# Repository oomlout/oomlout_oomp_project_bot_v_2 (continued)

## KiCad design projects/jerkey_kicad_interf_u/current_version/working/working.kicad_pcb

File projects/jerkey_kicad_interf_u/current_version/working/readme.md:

# kicad
 
## summary 
* id: jerkey_kicad_interf_u
* user: jerkey
* name: kicad
* board: interf_u
* repo: https://github.com/jerkey/kicad
* src_file_repo_kicad_pcb: demos/interf_u/interf_u.kicad_pcb
* src_file_repo_kicad_pcb_link: https://github.com/jerkey/kicad/tree/master/demos/interf_u/interf_u.kicad_pcb

* src_file_repo_sch: demos/interf_u/interf_u.sch
* src_file_repo_sch_link: https://github.com/jerkey/kicad/tree/master/demos/interf_u/interf_u.sch
* full details link: https://github.com/oomlout/oomlout_oomp_project_bot_v_2/tree/main/projects/jerkey_kicad_interf_u/current_version/working

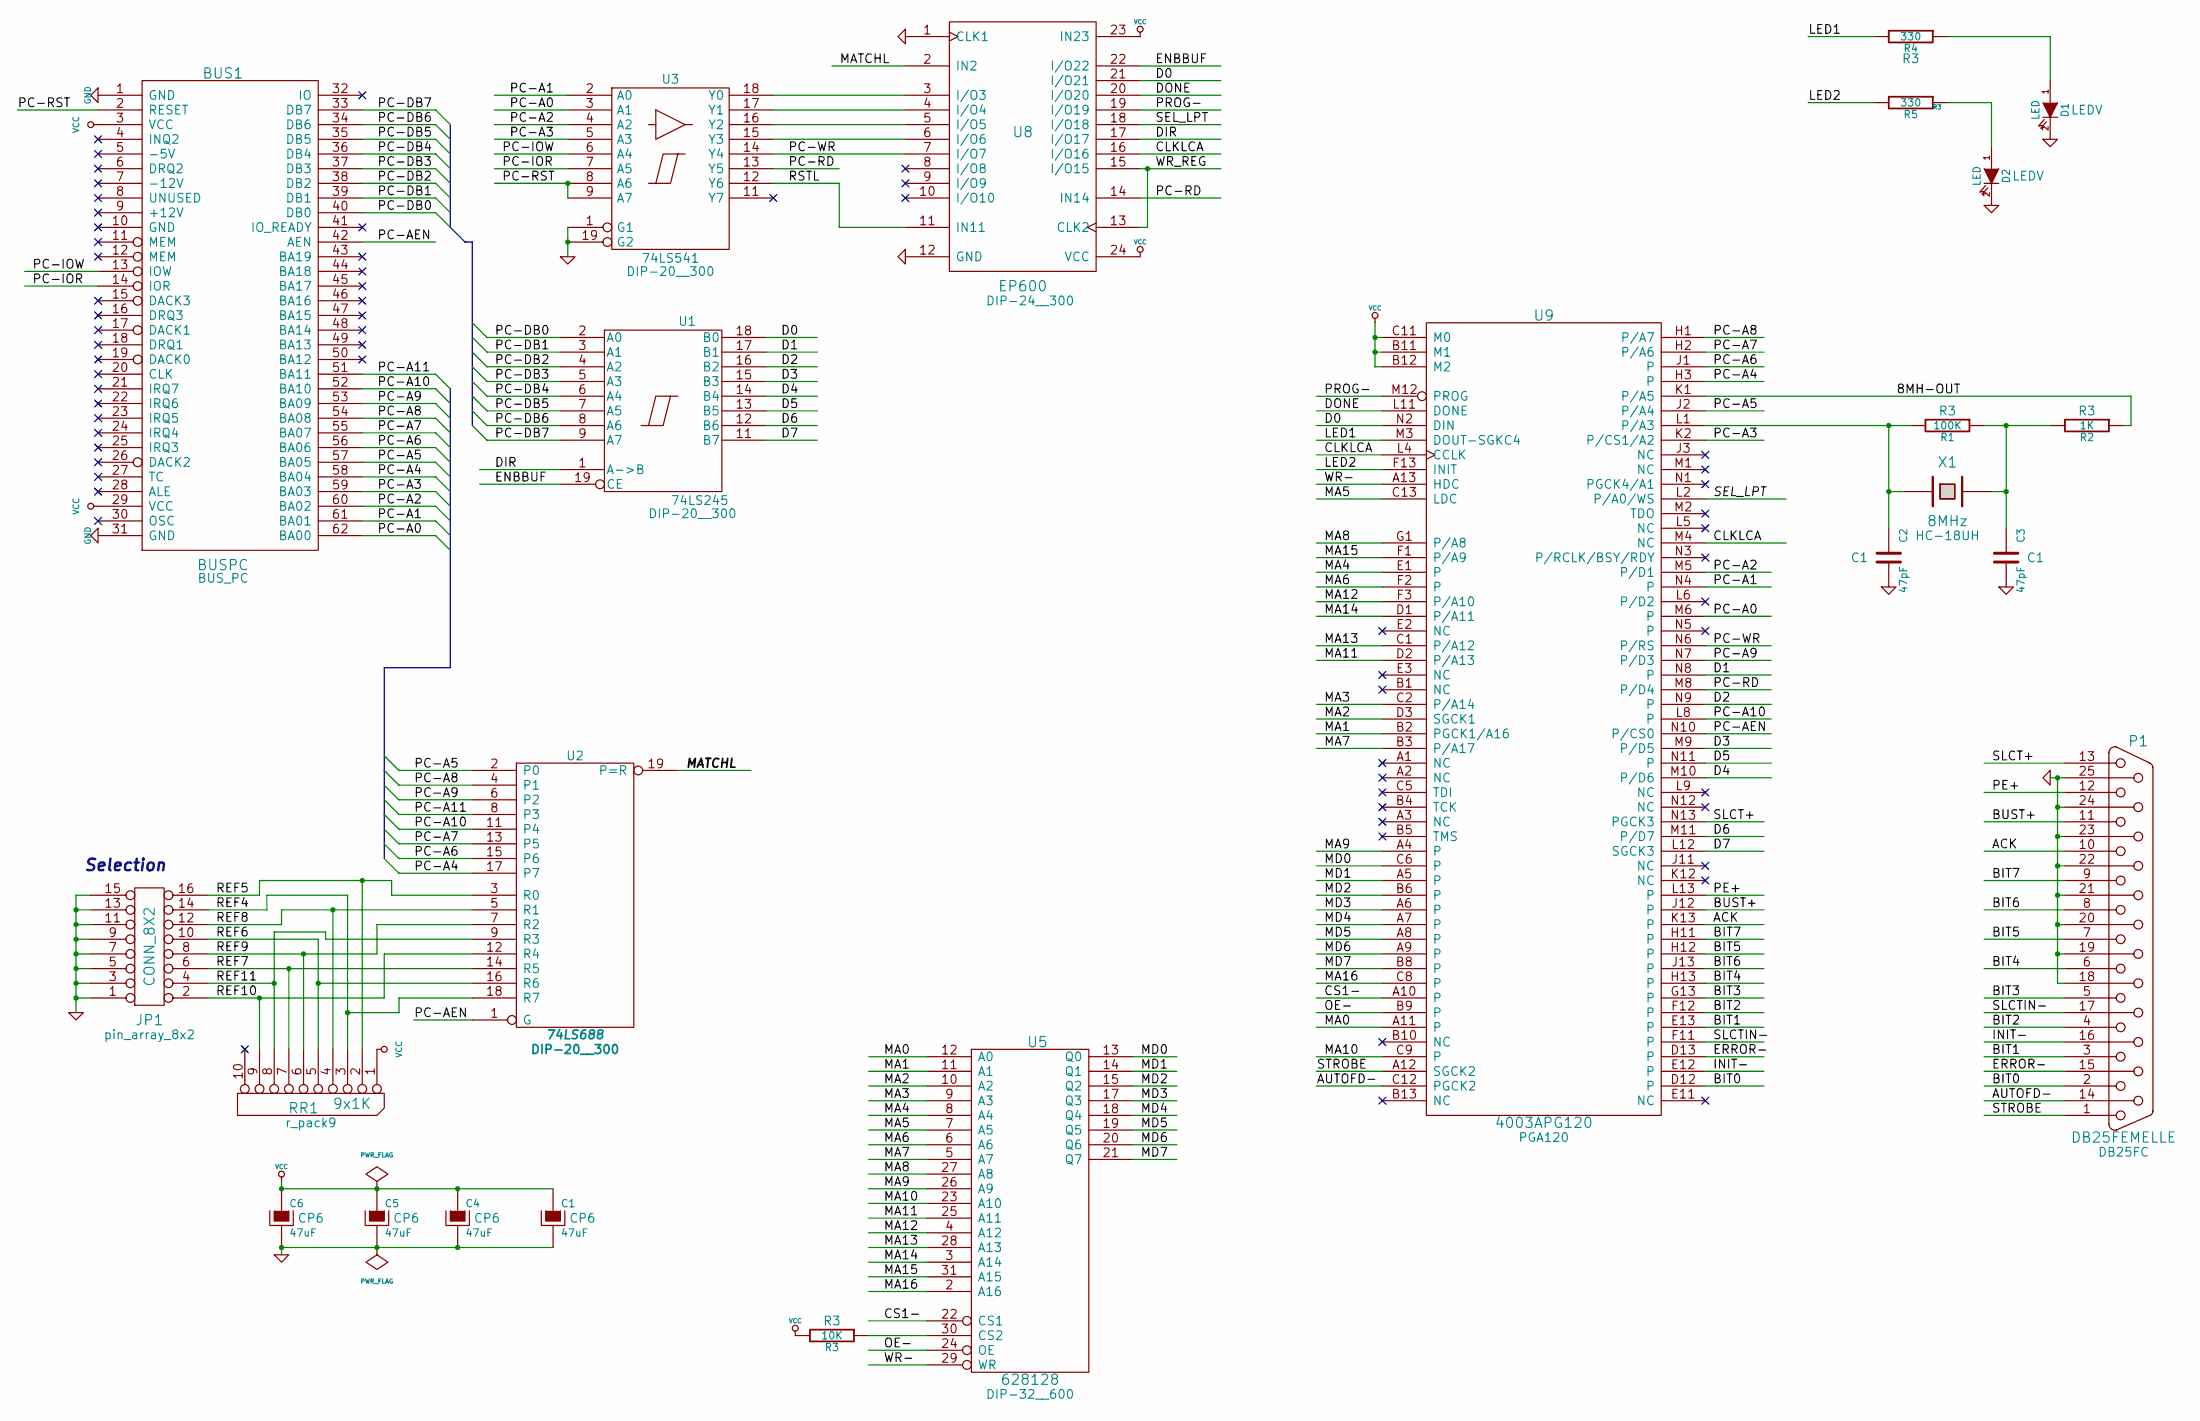
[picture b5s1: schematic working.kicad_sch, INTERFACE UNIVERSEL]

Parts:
BUS1: BUSPC; BUS_PC
C1, C4, C5, C6: 47uF; CP6
C2, C3: 47pF; C1
D1, D2: LED; LEDV
JP1: CONN_8X2; pin_array_8x2
P1: DB25FEMELLE; DB25FC
R1: 100K; R3
R2: 1K; R3
R3: 10K; R3
R4, R5: 330; R3
RR1: 9x1K; r_pack9
U1: 74LS245; DIP-20__300
U2: 74LS688; DIP-20__300
U3: 74LS541; DIP-20__300
U5: 628128; DIP-32__600
U8: EP600; DIP-24__300
U9: 4003APG120; PGA120
X1: 8MHz; HC-18UH

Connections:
/8MH-OUT: R2.1, U9.K1 (P/A5)
/ACK: P1.10, U9.K13
/AUTOFD-: P1.14, U9.C12 (PGCK2)
/BIT0: P1.2, U9.D12
/BIT1: P1.3, U9.E13
/BIT2: P1.4, U9.F12
/BIT3: P1.5, U9.G13
/BIT4: P1.6, U9.H13
/BIT5: P1.7, U9.H12
/BIT6: P1.8, U9.J13
/BIT7: P1.9, U9.H11
/BUST+: P1.11, U9.J12
/CLKLCA: U8.16 (I/O16), U9.L4 (CCLK), U9.M4 (NC)
/CS1-: U5.22 (CS1), U9.A10
/D0: U1.18 (B0), U8.21 (I/O21), U9.N2 (DIN)
/D1: U1.17 (B1), U9.N8
/D2: U1.16 (B2), U9.N9
/D3: U1.15 (B3), U9.M9 (P/D5)
/D4: U1.14 (B4), U9.M10 (P/D6)
/D5: U1.13 (B5), U9.N11
/D6: U1.12 (B6), U9.M11 (P/D7)
/D7: U1.11 (B7), U9.L12 (SGCK3)
/DIR: U1.1 (A->B), U8.17 (I/O17)
/DONE: U8.20 (I/O20), U9.L11 (DONE)
/ENBBUF: U1.19 (CE), U8.22 (I/O22)
/ERROR-: P1.15, U9.D13
/INIT-: P1.16, U9.E12
/LED1: R4.2, U9.M3 (DOUT-SGKC4)
/LED2: R5.2, U9.F13 (INIT)
/MA0: U5.12 (A0), U9.A11
/MA1: U5.11 (A1), U9.B2 (PGCK1/A16)
/MA2: U5.10 (A2), U9.D3 (SGCK1)
/MA3: U5.9 (A3), U9.C2 (P/A14)
/MA4: U5.8 (A4), U9.E1
/MA5: U5.7 (A5), U9.C13 (LDC)
/MA6: U5.6 (A6), U9.F2
/MA7: U5.5 (A7), U9.B3 (P/A17)
/MA8: U5.27 (A8), U9.G1 (P/A8)
/MA9: U5.26 (A9), U9.A4
/MA10: U5.23 (A10), U9.C9
/MA11: U5.25 (A11), U9.D2 (P/A13)
/MA12: U5.4 (A12), U9.F3 (P/A10)
/MA13: U5.28 (A13), U9.C1 (P/A12)
/MA14: U5.3 (A14), U9.D1 (P/A11)
/MA15: U5.31 (A15), U9.F1 (P/A9)
/MA16: U5.2 (A16), U9.C8
/MATCHL: U2.19 (P=R), U8.2 (IN2)
/MD0: U5.13 (Q0), U9.C6
/MD1: U5.14 (Q1), U9.A5
/MD2: U5.15 (Q2), U9.B6
/MD3: U5.17 (Q3), U9.A6
/MD4: U5.18 (Q4), U9.A7
/MD5: U5.19 (Q5), U9.A8
/MD6: U5.20 (Q6), U9.A9
/MD7: U5.21 (Q7), U9.B8
/OE-: U5.24 (OE), U9.B9
/PC-A0: BUS1.62 (BA00), U3.3 (A1), U9.M6
/PC-A1: BUS1.61 (BA01), U3.2 (A0), U9.N4
/PC-A2: BUS1.60 (BA02), U3.4 (A2), U9.M5 (P/D1)
/PC-A3: BUS1.59 (BA03), U3.5 (A3), U9.K2 (P/CS1/A2)
/PC-A4: BUS1.58 (BA04), U2.17 (P7), U9.H3
/PC-A5: BUS1.57 (BA05), U2.2 (P0), U9.J2 (P/A4)
/PC-A6: BUS1.56 (BA06), U2.15 (P6), U9.J1
/PC-A7: BUS1.55 (BA07), U2.13 (P5), U9.H2 (P/A6)
/PC-A8: BUS1.54 (BA08), U2.4 (P1), U9.H1 (P/A7)
/PC-A9: BUS1.53 (BA09), U2.6 (P2), U9.N7 (P/D3)
/PC-A10: BUS1.52 (BA10), U2.11 (P4), U9.L8
/PC-A11: BUS1.51 (BA11), U2.8 (P3)
/PC-AEN: BUS1.42 (AEN), U2.1 (G), U9.N10 (P/CS0)
/PC-DB0: BUS1.40 (DB0), U1.2 (A0)
/PC-DB1: BUS1.39 (DB1), U1.3 (A1)
/PC-DB2: BUS1.38 (DB2), U1.4 (A2)
/PC-DB3: BUS1.37 (DB3), U1.5 (A3)
/PC-DB4: BUS1.36 (DB4), U1.6 (A4)
/PC-DB5: BUS1.35 (DB5), U1.7 (A5)
/PC-DB6: BUS1.34 (DB6), U1.8 (A6)
/PC-DB7: BUS1.33 (DB7), U1.9 (A7)
/PC-IOR: BUS1.14 (IOR), U3.7 (A5)
/PC-IOW: BUS1.13 (IOW), U3.6 (A4)
/PC-RD: U3.13 (Y5), U8.14 (IN14), U9.M8 (P/D4)
/PC-RST: BUS1.2 (RESET), U3.8 (A6), U3.9 (A7)
/PC-WR: U3.14 (Y4), U8.7 (I/O7), U9.N6 (P/RS)
/PE+: P1.12, U9.L13
/PROG-: U8.19 (I/O19), U9.M12 (PROG)
/REF4: JP1.14, RR1.3, U2.18 (R7)
/REF5: JP1.16, RR1.2, U2.3 (R0)
/REF6: JP1.10, RR1.5, U2.16 (R6)
/REF7: JP1.6, RR1.7, U2.14 (R5)
/REF8: JP1.12, RR1.4, U2.5 (R1)
/REF9: JP1.8, RR1.6, U2.7 (R2)
/REF10: JP1.2, RR1.9, U2.12 (R4)
/REF11: JP1.4, RR1.8, U2.9 (R3)
/RSTL: U3.12 (Y6), U8.11 (IN11)
/SEL_LPT: U8.18 (I/O18), U9.L2 (P/A0/WS)
/SLCT+: P1.13, U9.N13 (PGCK3)
/SLCTIN-: P1.17, U9.F11
/STROBE: P1.1, U9.A12 (SGCK2)
/WR-: U5.29 (WR), U9.A13 (HDC)
/WR_REG: U8.13 (CLK2), U8.15 (I/O15)
GND: BUS1.1 (GND), BUS1.31 (GND), C1.2, C2.2, C3.2, C4.2, C5.2, C6.2, D1.2 (K), D2.2 (K), JP1.1, JP1.3, JP1.5, JP1.7, JP1.9, JP1.11, JP1.13, JP1.15, P1.18, P1.19, P1.20, P1.21, P1.22, P1.23, P1.24, P1.25, U1.10 (GND), U2.10 (GND), U3.1 (G1), U3.10 (GND), U3.19 (G2), U5.16 (GND), U8.1 (CLK1), U8.12 (GND), U9.B7 (GND), U9.C4 (GND), U9.C10 (GND), U9.G2 (GND), U9.G11 (GND), U9.K3 (GND), U9.K11 (GND), U9.L7 (GND)
unnamed: R3.1, U5.30 (CS2)
unnamed: D2.1 (A), R5.1
unnamed: D1.1 (A), R4.1
unnamed: U3.18 (Y0), U8.3 (I/O3)
unnamed: U3.17 (Y1), U8.4 (I/O4)
unnamed: U3.16 (Y2), U8.5 (I/O5)
unnamed: U3.15 (Y3), U8.6 (I/O6)
unnamed: C2.1, R1.2, U9.L1 (P/A3), X1.1
unnamed: C3.1, R1.1, R2.2, X1.2
VCC: BUS1.3 (VCC), BUS1.29 (VCC), C1.1, C4.1, C5.1, C6.1, R3.2, RR1.1 (COM), U1.20 (VCC), U2.20 (VCC), U3.20 (VCC), U5.32 (VCC), U8.23 (IN23), U8.24 (VCC), U9.B11 (M1), U9.B12 (M2), U9.C3 (VCC), U9.C11 (M0), U9.D11 (VCC), U9.G12 (VCC), U9.L3 (VCC), U9.L10 (VCC), U9.M7 (VCC)

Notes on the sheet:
Selection

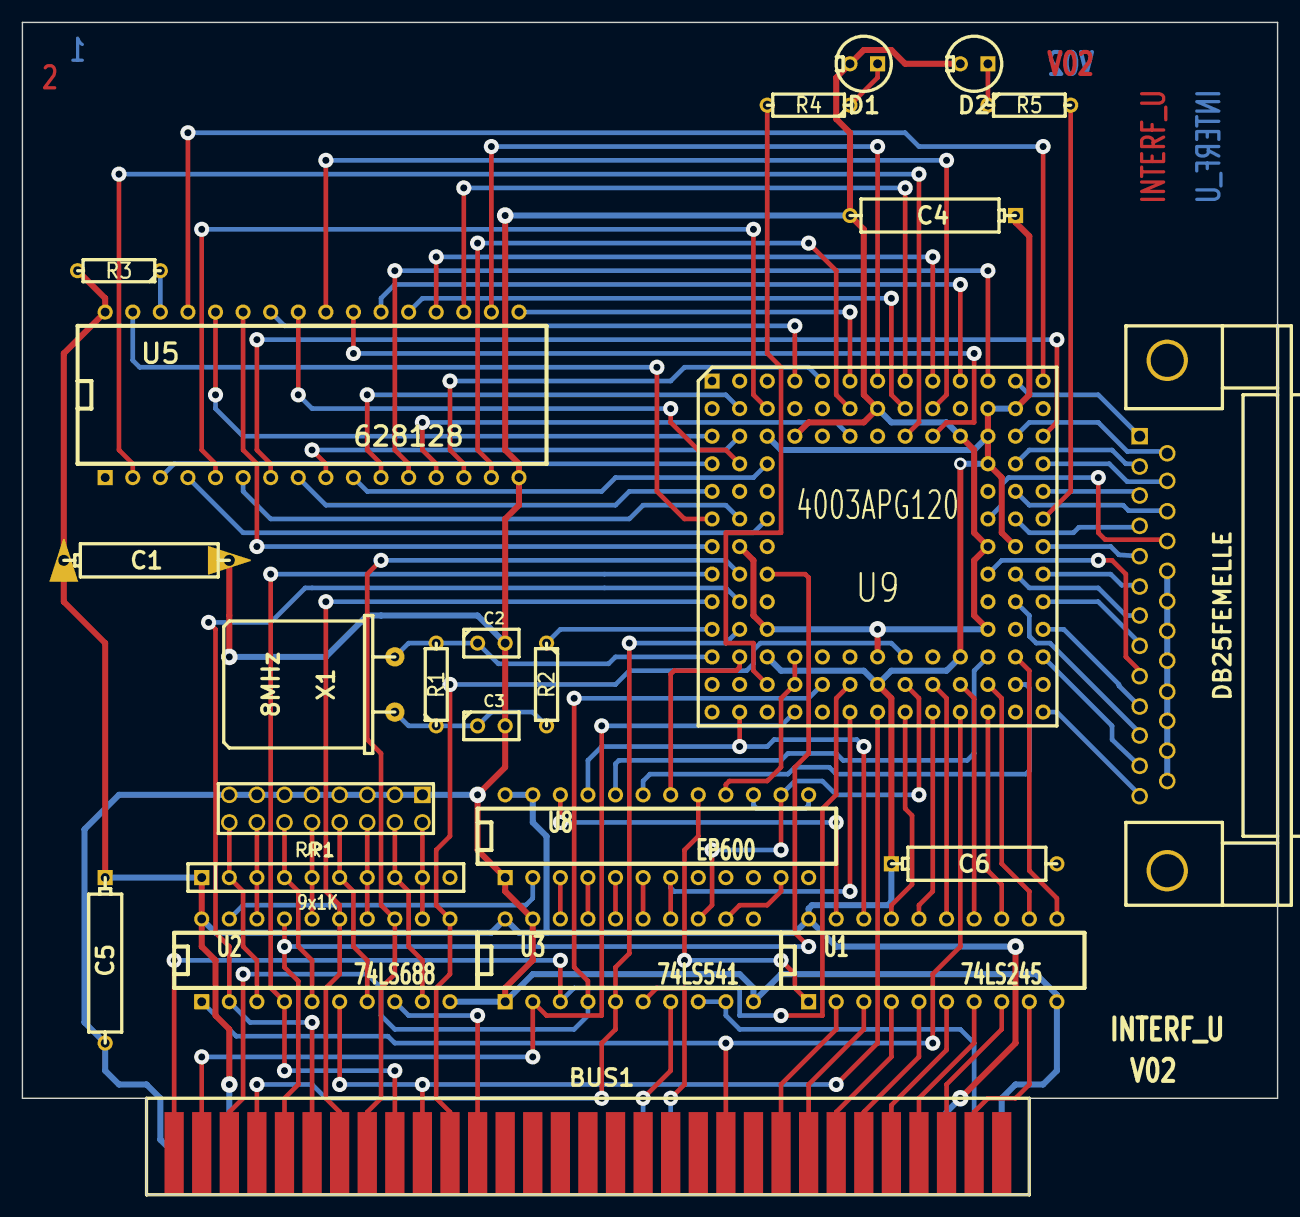
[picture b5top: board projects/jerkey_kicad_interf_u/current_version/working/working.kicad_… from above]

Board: 2 copper layers, 115.6 x 108.0 mm, 25 parts (0 on the bottom side), 110 nets.

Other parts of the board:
G1: LOGO

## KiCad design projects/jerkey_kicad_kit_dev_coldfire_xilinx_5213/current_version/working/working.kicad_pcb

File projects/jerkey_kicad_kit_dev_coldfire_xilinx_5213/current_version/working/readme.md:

# kicad
 
## summary 
* id: jerkey_kicad_kit_dev_coldfire_xilinx_5213
* user: jerkey
* name: kicad
* board: kit_dev_coldfire_xilinx_5213
* repo: https://github.com/jerkey/kicad
* src_file_repo_kicad_pcb: demos/kit-dev-coldfire-xilinx_5213/kit-dev-coldfire-xilinx_5213.kicad_pcb
* src_file_repo_kicad_pcb_link: https://github.com/jerkey/kicad/tree/master/demos/kit-dev-coldfire-xilinx_5213/kit-dev-coldfire-xilinx_5213.kicad_pcb

* src_file_repo_sch: demos/interf_u/interf_u.sch
* src_file_repo_sch_link: https://github.com/jerkey/kicad/tree/master/demos/interf_u/interf_u.sch
* full details link: https://github.com/oomlout/oomlout_oomp_project_bot_v_2/tree/main/projects/jerkey_kicad_kit_dev_coldfire_xilinx_5213/current_version/working

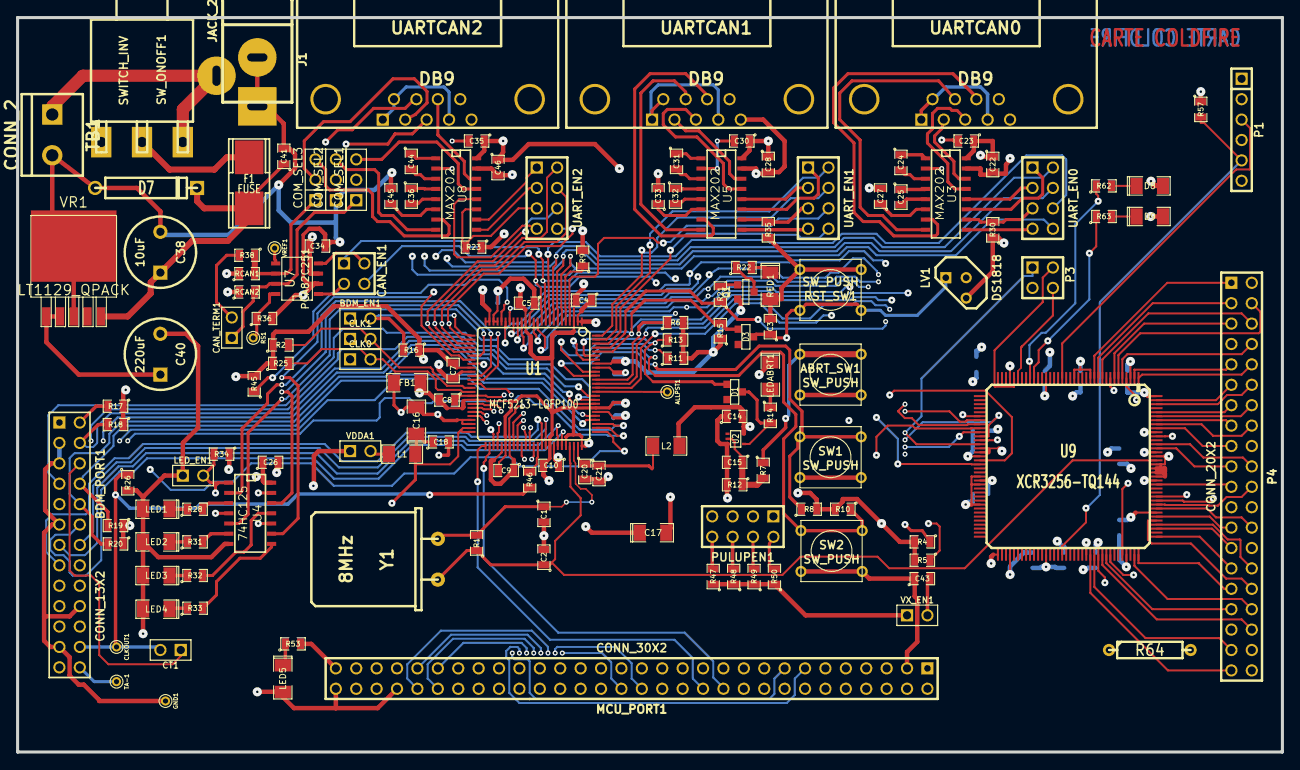
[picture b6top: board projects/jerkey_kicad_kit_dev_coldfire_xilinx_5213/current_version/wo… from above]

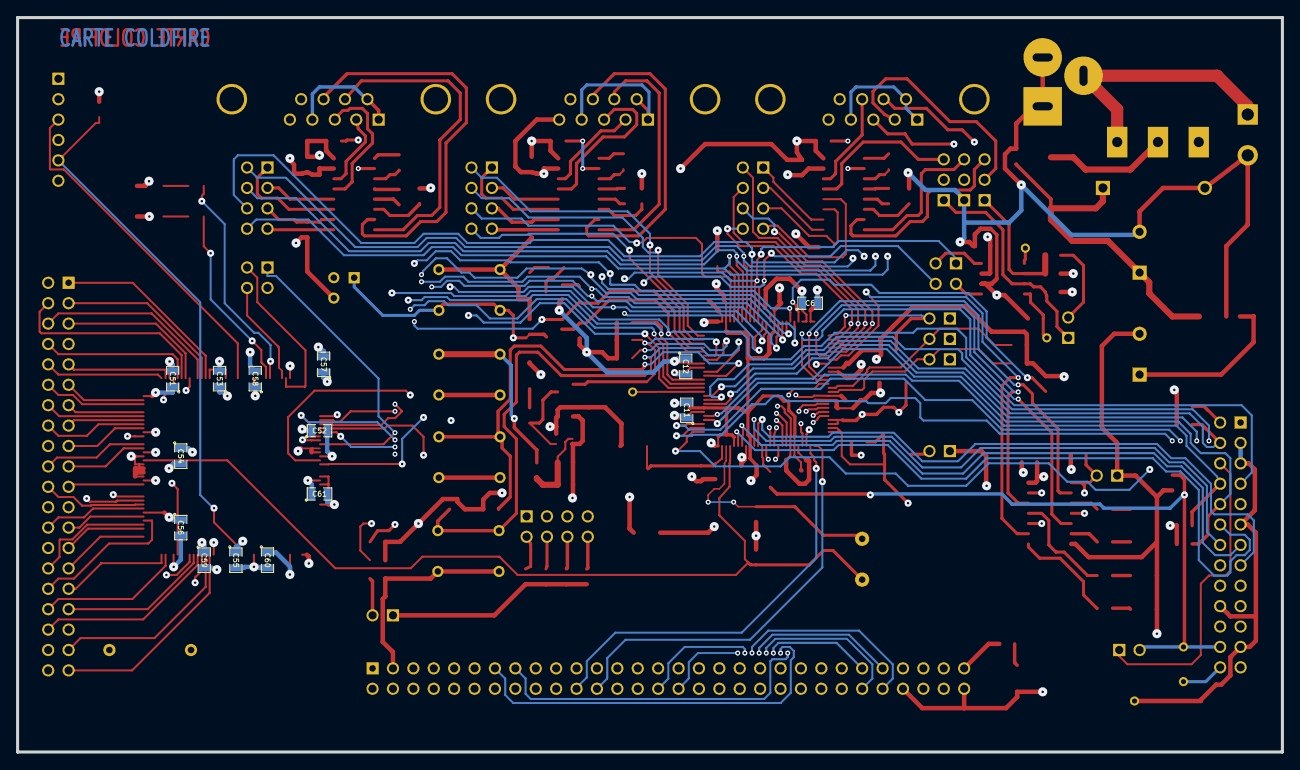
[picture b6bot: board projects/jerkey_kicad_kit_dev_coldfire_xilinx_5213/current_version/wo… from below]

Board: 4 copper layers, 157.5 x 91.4 mm, 162 parts (14 on the bottom side), 209 nets.

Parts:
ABRT_SW1: SW_PUSH; SW_PUSH_SMALL
ALLPST1: CONN_1; PINTST
BDM_EN1: JUMPER; PIN_ARRAY_2X1
BDM_PORT1: CONN_13X2; pin_array_13x2
C1, C2: 10pF; SM0805
C3, C20: 1nF; SM0805
C4, C5, C6, C7, C8, C9, C10, C11, C12, C14, C15, C18, C21, C22, C23, C24, C25, C26, C27, C28, C30, C31, C32, C33, C34, C35, C36, C41, C43, C44, C45, C46, C51, C52, C53, C54, C55, C56, C57, C58, C59, C60, C61: 100nF; SM0805
C16: 10uF; SM1206POL
C17: 100uF; SM1206POL
C38: 10uF; C2V8
C40: 220uF; C2V8
CAN_EN1: CONN_2X2; PIN_ARRAY_2X2
CAN_TERM1: JUMPER; PIN_ARRAY_2X1
CLK0, CLK1: JUMPER; PIN_ARRAY_2X1
CLKOUT1: CONN_1; PINTST
COM_SEL1, COM_SEL2, COM_SEL3: CONN_3; PIN_ARRAY_3X1
CT1: JUMPER; PIN_ARRAY_2X1
D1, D3: BAT54; ST23AK#1
D7: 1N4004; D5
D8, D9: LED; SM1206POL
F1: FUSE; FSUPCMS
FB1: BEAD; SM1206
GND1: CONN_1; PINTST
J1: JACK_2P; JACK_ALIM
L1, L2: 10uH; SM1206
LED1, LED2, LED3, LED4, LED5: LED; SM1206POL
LEDABRT1: RED; SM1206POL
LED_EN1: JUMPER; PIN_ARRAY_2X1
LV1: DS1818; TO92-INVERT
MCU_PORT1: CONN_30X2; PIN_ARRAY_30X2
P1: CONN_6; PIN_ARRAY-6X1
P3: CONN_2X2; PIN_ARRAY_2X2
P4: CONN_20X2; PIN_ARRAY_20X2
PULUPEN1: CONN_4X2; pin_array_4x2
Q1: 3906; SOT23EBC
R1: 1M; SM0805
R2, R15, R16, R17, R18, R19, R20, R21, R25, R45, R47, R48, R49, R50: 4,7K; SM0805
R4, R5, R6, R8, R10, R11, R13, R23, R26, R30, R34, R35: 10K; SM0805
R7, R36, R62, R63: 1K; SM0805
R9: 0; SM0805
R12: 20K; SM0805
R14, R22, R28, R31, R32, R33, R53: 270; SM0805
R38: 62; SM0805
R46: 22; SM0805
R57: 4K7; SM0805
R64: 3,3; R4
RCAN1, RCAN2: R; SM0805
RED1: LED_RESET1; SM1206POL
RS1: CONN_1; PINTST
RST_SW1: SW_PUSH; SW_PUSH_SMALL
SW1, SW2: SW_PUSH; SW_PUSH_SMALL
SW_ONOFF1: SWITCH_INV; SW_SPDT
TA-1: CONN_1; PINTST
TB1: CONN_2; bornier2
U1: MCF5213-LQFP100; VQFP100
U2: 74AHC1G14; SOT353
U3, U5, U8: MAX202; SO16E
U4: 74HC125; SO14E
U7: PCA82C251; SO8E
U9: XCR3256-TQ144; TQFP144
UARTCAN0, UARTCAN1, UARTCAN2: DB9; DB9FC
UART_EN0, UART_EN1, UART_EN2: CONN_4X2; pin_array_4x2
VDDA1: JUMPER; PIN_ARRAY_2X1
VR1: LT1129_QPACK; DPAK5
VREF1: CONN_1; PINTST
VX_EN1: JUMPER; PIN_ARRAY_2X1
Y1: 8MHz; HC-18UH

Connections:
/ALLPST: ALLPST1.1, U1.86
/AN0: MCU_PORT1.10, U1.43
/AN1: MCU_PORT1.12, U1.44
/AN2: MCU_PORT1.14, U1.45
/AN3: MCU_PORT1.16, U1.46
/AN4: MCU_PORT1.18, U1.54
/AN5: MCU_PORT1.20, U1.53
/AN6: MCU_PORT1.22, U1.52
/AN7: MCU_PORT1.24, U1.51
/BKPT-: BDM_PORT1.2, R17.2, U1.76
/CLKIN/EXTAL: C1.1, R1.2, U1.73, Y1.1
/CLKMOD0: CLK0.2, R25.2, U1.40
/CLKMOD1: CLK1.2, R2.2, U1.39
/DDAT0: BDM_PORT1.19, U1.77
/DDAT1: BDM_PORT1.18, U1.78
/DDAT2: BDM_PORT1.17, U1.83
/DDAT3: BDM_PORT1.16, U1.84
/DSCLK: BDM_PORT1.4, R18.2, U1.85
/DSI: BDM_PORT1.8, R19.2, U1.79
/DSO: BDM_PORT1.10, R20.2, U1.80
/DTIN0: MCU_PORT1.34, U1.36, U4.2
/DTIN1: MCU_PORT1.36, U1.37, U4.5
/DTIN2: MCU_PORT1.38, U1.31, U4.12
/DTIN3: MCU_PORT1.40, U1.32, U4.9
/GPT0: MCU_PORT1.49, U1.58
/GPT1: MCU_PORT1.50, U1.59
/GPT2: MCU_PORT1.51, U1.61
/GPT3: MCU_PORT1.52, U1.62
/IRQ-4: MCU_PORT1.33, R8.1, SW1.1, U1.90
/IRQ-5: MCU_PORT1.35, R10.1, SW2.1, U1.91
/IRQ-6: MCU_PORT1.37, R11.1, U1.94
/IRQ-7: D1.1, MCU_PORT1.39, R13.1, U1.95
/JTAG_EN: BDM_EN1.2, R16.2, U1.26
/PST0: BDM_PORT1.15, U1.65
/PST1: BDM_PORT1.14, U1.66
/PST2: BDM_PORT1.13, U1.69
/PST3: BDM_PORT1.12, U1.70
/QSPI_CS0: MCU_PORT1.23, PULUPEN1.3, U1.20
/QSPI_CS3: MCU_PORT1.29, U1.12
/TCLK: BDM_PORT1.24, CLKOUT1.1, CT1.2, R26.1, R46.2
/VDDPLL: C20.1, C21.1, L2.2, U1.74
/inout_user/CANRX: CAN_EN1.4, MCU_PORT1.28, PULUPEN1.7, U1.11
/inout_user/CANTX: CAN_EN1.1, MCU_PORT1.26, PULUPEN1.5, U1.10
/inout_user/CAN_H: CAN_TERM1.1, COM_SEL1.1, RCAN2.2, U7.7
/inout_user/CAN_L: COM_SEL3.1, R38.1, RCAN1.2, U7.6
/inout_user/CTS0: U3.8, UARTCAN0.7
/inout_user/CTS1: U5.8, UARTCAN1.7
/inout_user/CTS2/CANH: COM_SEL1.2, UARTCAN2.7
/inout_user/PWM1: MCU_PORT1.13, U1.38
/inout_user/PWM3: MCU_PORT1.15, U1.33
/inout_user/PWM5: MCU_PORT1.30, U1.60
/inout_user/PWM7: MCU_PORT1.32, U1.63
/inout_user/QSPI_DIN: MCU_PORT1.19, U1.16, U9.46
/inout_user/QSPI_DOUT: MCU_PORT1.17, U1.17, U9.47
/inout_user/QSPI_SCLK: MCU_PORT1.21, PULUPEN1.1, U1.18, U9.48
/inout_user/RCON-: MCU_PORT1.53, R45.1, U1.21
/inout_user/RSTI-: BDM_PORT1.7, D3.1, MCU_PORT1.6, R15.2, U1.96
/inout_user/RTS0: U3.7, UARTCAN0.8
/inout_user/RTS0-: MCU_PORT1.4, R21.1, U1.97
/inout_user/RTS1: U5.7, UARTCAN1.8
/inout_user/RTS2: U8.14, UARTCAN2.8
/inout_user/RXD0: U3.13, UARTCAN0.3
/inout_user/RXD1: U5.13, UARTCAN1.3
/inout_user/RXD2: COM_SEL2.2, UARTCAN2.3
/inout_user/RxD_CAN: CAN_EN1.2, U7.4
/inout_user/TXD0: U3.14, UARTCAN0.2
/inout_user/TXD1: U5.14, UARTCAN1.2
/inout_user/TXD2/CANL: COM_SEL3.2, UARTCAN2.2
/inout_user/TxD_CAN: CAN_EN1.3, U7.1
/inout_user/UCTS0: MCU_PORT1.44, U1.6, UART_EN0.8
/inout_user/UCTS1: MCU_PORT1.11, P3.1, U1.98, U9.49, UART_EN1.8
/inout_user/UCTS2: MCU_PORT1.48, U1.27, UART_EN2.8
/inout_user/URTS0: MCU_PORT1.42, U1.9, UART_EN0.6
/inout_user/URTS1: MCU_PORT1.9, P3.3, U1.4, U9.53, UART_EN1.6
/inout_user/URTS2: MCU_PORT1.46, U1.30, UART_EN2.6
/inout_user/URXD0: MCU_PORT1.43, U1.7, UART_EN0.4
/inout_user/URXD1: MCU_PORT1.7, U1.100, UART_EN1.4
/inout_user/URXD2: MCU_PORT1.47, U1.28, UART_EN2.4
/inout_user/UTXD0: MCU_PORT1.41, U1.8, UART_EN0.2
/inout_user/UTXD1: MCU_PORT1.5, U1.99, UART_EN1.2
/inout_user/UTXD2: MCU_PORT1.45, U1.29, UART_EN2.2
/inout_user/VCCA: C16.1, C18.1, L1.2, MCU_PORT1.55, MCU_PORT1.57, U1.49, U1.50
/xilinx/+3,3V_OUT: P4.38, R64.2
/xilinx/GLCK2: C2.1, R1.1, U1.72, U9.128, Y1.2
/xilinx/IRQ-1: MCU_PORT1.2, R4.1, U1.87, U9.42
/xilinx/IRQ-2: MCU_PORT1.8, R5.1, U1.88, U9.43
/xilinx/IRQ-3: MCU_PORT1.31, R6.1, U1.89, U9.44
/xilinx/LED_TEST1: R62.1, U9.28
/xilinx/LED_TEST2: R63.1, U9.27
/xilinx/QSPI_CS1: MCU_PORT1.25, U1.19, U9.54
/xilinx/QSPI_CS2: MCU_PORT1.27, U1.13, U9.45
/xilinx/TCK: P1.5, R57.2, U9.89
/xilinx/TDI: P1.4, U9.4
/xilinx/TDO: P1.6, U9.104
/xilinx/TMS: P1.3, U9.20
/xilinx/XIL_D0: P4.1, U9.12
/xilinx/XIL_D1: P4.3, U9.11
/xilinx/XIL_D2: P4.5, U9.7
/xilinx/XIL_D3: P4.7, U9.8
/xilinx/XIL_D4: P4.9, U9.2
/xilinx/XIL_D5: P4.11, U9.143
/xilinx/XIL_D6: P4.13, U9.140
/xilinx/XIL_D7: P4.15, U9.138
/xilinx/XIL_D8: P4.17, U9.136
/xilinx/XIL_D9: P4.19, U9.131
/xilinx/XIL_D10: P4.21, U9.122
/xilinx/XIL_D11: P4.23, U9.119
/xilinx/XIL_D12: P4.25, U9.114
/xilinx/XIL_D13: P4.27, U9.111
/xilinx/XIL_D14: P4.29, U9.109
/xilinx/XIL_D15: P4.31, U9.108
/xilinx/XIL_D16: P4.33, U9.100
/xilinx/XIL_D17: P4.35, U9.101
/xilinx/XIL_D18: P4.37, U9.97
/xilinx/XIL_D19: P4.39, U9.96
/xilinx/XIL_D20: P4.4, U9.6
/xilinx/XIL_D21: P4.6, U9.10
/xilinx/XIL_D22: P4.8, U9.5
/xilinx/XIL_D23: P4.10, U9.1
/xilinx/XIL_D24: P4.12, U9.142
/xilinx/XIL_D25: P4.14, U9.139
/xilinx/XIL_D26: P4.16, U9.137
/xilinx/XIL_D27: P4.18, U9.134
/xilinx/XIL_D28: P4.20, U9.132
/xilinx/XIL_D29: P4.22, U9.117
/xilinx/XIL_D30: P4.24, U9.118
/xilinx/XIL_D31: P4.26, U9.116
/xilinx/XIL_D32: P4.28, U9.98
/xilinx/XIL_D33: P4.30, U9.112
/xilinx/XIL_D34: P4.32, U9.113
/xilinx/XIL_D35: P4.34, U9.107
/xilinx/XIL_D36: P4.36, U9.99
GND: BDM_EN1.1, BDM_PORT1.3, BDM_PORT1.5, BDM_PORT1.11, BDM_PORT1.20, BDM_PORT1.23, C1.2, C2.2, C3.2, C4.2, C5.2, C6.2, C7.2, C8.2, C9.2, C10.2, C11.2, C12.2, C14.1, C15.2, C17.2, C20.2, C21.2, C22.2, C26.2, C27.2, C28.2, C33.2, C34.2, C38.2, C40.2, C41.2, C43.1, C45.2, C46.2, C51.2, C52.2, C53.2, C54.2, C55.2, C56.2, C57.2, C58.2, C59.2, C60.2, C61.2, CLK0.1, CLK1.1, COM_SEL2.1, D7.1, D8.2, D9.2, FB1.1, GND1.1, J1.1, J1.2, LED1.2, LED2.2, LED3.2, LED4.2, LED5.2, LED_EN1.1, LV1.3, MCU_PORT1.3, MCU_PORT1.54, MCU_PORT1.60, P1.2, P4.2, P4.40, R9.2, R12.2, R23.1, R26.2, R30.1, R35.1, R36.2, RCAN2.1, RED1.2, RST_SW1.2, SW1.2, SW2.2, TB1.2, U1.3, U1.15, U1.24, U1.25, U1.35, U1.42, U1.56, U1.67, U1.71, U1.75, U1.82, U1.92, U2.3, U3.15, U4.7, U5.15, U7.2, U8.15, U9.3, U9.13, U9.17, U9.33, U9.52, U9.57, U9.59, U9.64, U9.85, U9.105, U9.124, U9.125, U9.126, U9.127, U9.129, U9.135, UARTCAN0.5, UARTCAN1.5, UARTCAN2.5, VR1.3
GNDA: C16.2, C18.2, FB1.2, MCU_PORT1.56, MCU_PORT1.58, U1.47, U1.48
unnamed: ABRT_SW1.1, R7.1
unnamed: BDM_PORT1.6, CT1.1
unnamed: BDM_PORT1.26, TA-1.1
unnamed: C3.1, D3.2, LV1.1, RST_SW1.1
unnamed: C15.1, R7.2, R12.1, U2.2
unnamed: C23.2, U3.2
unnamed: C24.1, U3.1
unnamed: C24.2, U3.3
unnamed: C25.1, U3.4
unnamed: C25.2, U3.5
unnamed: C27.1, U3.6
unnamed: C30.2, U5.2
unnamed: C31.1, U5.1
unnamed: C31.2, U5.3
unnamed: C32.1, U5.4
unnamed: C32.2, U5.5
unnamed: C33.1, U5.6
unnamed: C35.2, U8.2
unnamed: C36.1, U8.4
unnamed: C36.2, U8.5
unnamed: C38.1, C41.1, D7.2, F1.2, VR1.5
unnamed: C43.2, MCU_PORT1.1, VX_EN1.2
unnamed: C44.1, U8.1
unnamed: C44.2, U8.3
unnamed: C45.1, U8.6
unnamed: CAN_TERM1.2, R38.2
unnamed: COM_SEL1.3, U8.13
unnamed: COM_SEL2.3, U8.8
unnamed: COM_SEL3.3, U8.7
unnamed: D1.2, R14.2, U2.4
unnamed: D8.1, R62.2
unnamed: D9.1, R63.2
unnamed: F1.1, SW_ONOFF1.2
unnamed: J1.3, SW_ONOFF1.3, TB1.1
unnamed: L1.1, VDDA1.2
unnamed: LED1.1, R28.1
unnamed: LED2.1, R31.1
unnamed: LED3.1, R32.1
unnamed: LED4.1, R33.1
unnamed: LED5.1, R53.1
unnamed: LEDABRT1.2, R14.1
unnamed: LED_EN1.2, R34.2, U4.1, U4.4, U4.10, U4.13
unnamed: P3.2, U9.32
unnamed: P3.4, U9.31
unnamed: PULUPEN1.2, R50.2
unnamed: PULUPEN1.4, R49.2
unnamed: PULUPEN1.6, R48.2
unnamed: PULUPEN1.8, R47.2
unnamed: Q1.2, R21.2
unnamed: Q1.3, R22.1
unnamed: R9.1, U1.5
unnamed: R22.2, RED1.1
unnamed: R23.2, U8.11, UART_EN2.5
unnamed: R28.2, U4.3
unnamed: R30.2, U3.10, UART_EN0.5
unnamed: R31.2, U4.6
unnamed: R32.2, U4.11
unnamed: R33.2, U4.8
unnamed: R35.2, U5.10, UART_EN1.5
unnamed: R36.1, RS1.1, U7.8
unnamed: R46.1, U1.64
unnamed: U3.9, UART_EN0.7
unnamed: U3.11, UART_EN0.1
unnamed: U3.12, UART_EN0.3
unnamed: U5.9, UART_EN1.7
unnamed: U5.11, UART_EN1.1
unnamed: U5.12, UART_EN1.3
unnamed: U7.5, VREF1.1
unnamed: U8.9, UART_EN2.3
unnamed: U8.10, UART_EN2.1
unnamed: U8.12, UART_EN2.7
unnamed: UARTCAN0.1, UARTCAN0.4, UARTCAN0.6
unnamed: UARTCAN1.1, UARTCAN1.4, UARTCAN1.6
unnamed: UARTCAN2.1, UARTCAN2.4, UARTCAN2.6
VDD: ABRT_SW1.2, BDM_PORT1.9, BDM_PORT1.25, C4.1, C5.1, C6.1, C7.1, C8.1, C9.1, C10.1, C11.1, C12.1, C14.2, C17.1, C22.1, C23.1, C26.1, C28.1, C30.1, C34.1, C35.1, C40.1, C46.1, C51.1, C52.1, C53.1, C54.1, C55.1, C56.1, C57.1, C58.1, C59.1, C60.1, C61.1, L2.1, LEDABRT1.1, LV1.2, MCU_PORT1.59, P1.1, Q1.1, R2.1, R4.2, R5.2, R6.2, R8.2, R10.2, R11.2, R13.2, R15.1, R16.1, R17.1, R18.1, R19.1, R20.1, R25.1, R34.1, R45.2, R47.1, R48.1, R49.1, R50.1, R53.2, R57.1, R64.1, RCAN1.1, U1.1, U1.2, U1.14, U1.22, U1.23, U1.34, U1.41, U1.55, U1.57, U1.68, U1.81, U1.93, U2.5, U3.16, U4.14, U5.16, U7.3, U8.16, U9.24, U9.50, U9.51, U9.58, U9.73, U9.76, U9.95, U9.115, U9.123, U9.130, U9.144, VDDA1.1, VR1.1, VR1.2, VX_EN1.1
